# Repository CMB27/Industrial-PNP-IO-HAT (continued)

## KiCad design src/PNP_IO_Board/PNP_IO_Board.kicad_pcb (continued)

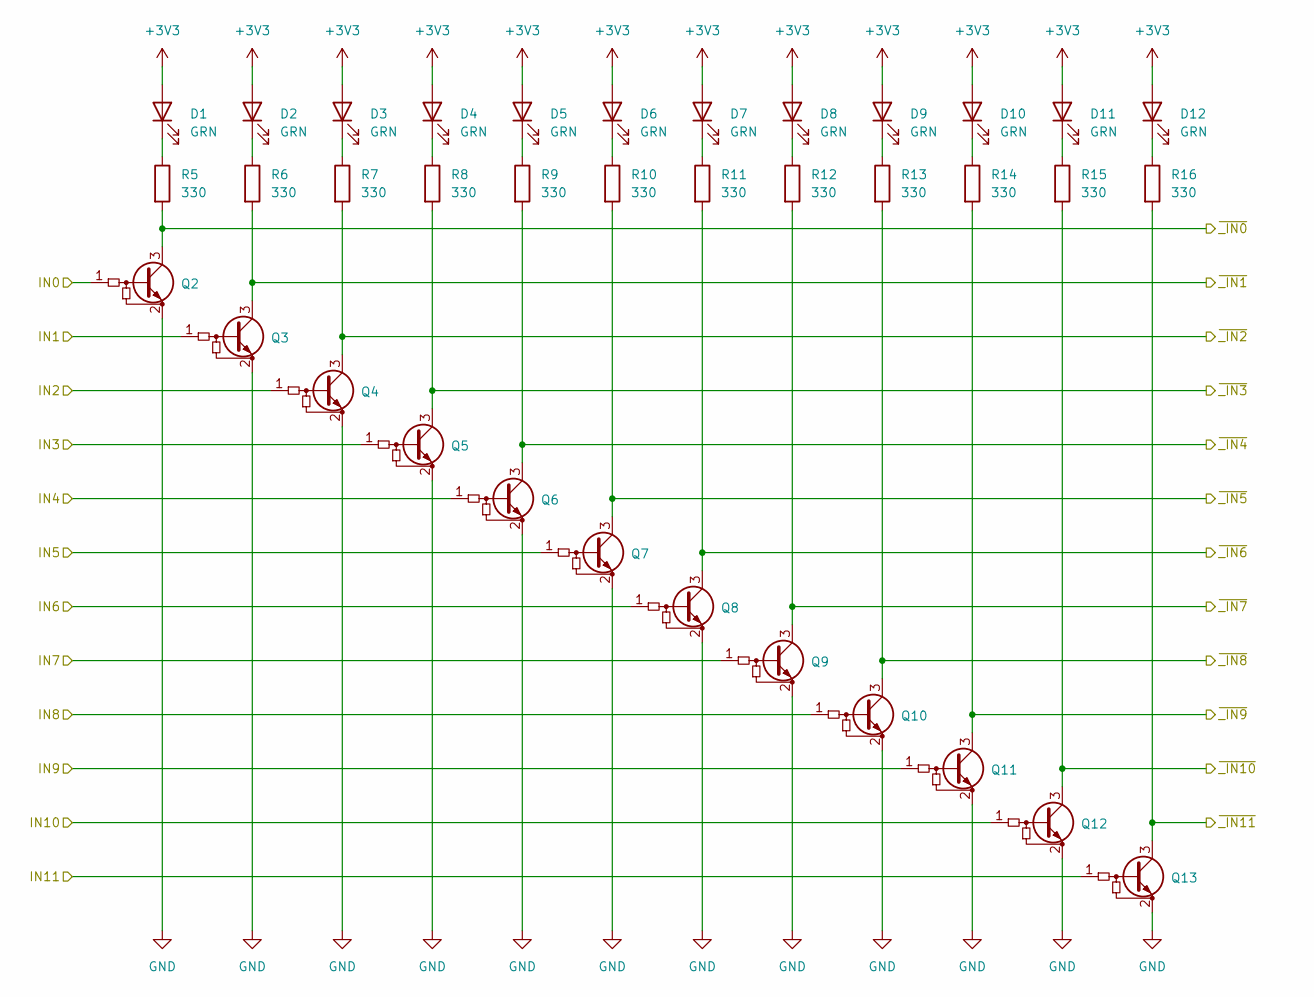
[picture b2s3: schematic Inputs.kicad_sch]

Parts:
D1, D2, D3, D4, D5, D6, D7, D8, D9, D10, D11, D12: GRN; LED_5mm_Green
Q2, Q3, Q4, Q5, Q6, Q7, Q8, Q9, Q10, Q11, Q12, Q13: Q_NPN_BRT_BEC; SOT-23
R5, R6, R7, R8, R9, R10, R11, R12, R13, R14, R15, R16: 330; R_1206_3216Metric_Pad1.30x1.75mm_HandSolder

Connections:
+3V3: D1.2 (A), D2.2 (A), D3.2 (A), D4.2 (A), D5.2 (A), D6.2 (A), D7.2 (A), D8.2 (A), D9.2 (A), D10.2 (A), D11.2 (A), D12.2 (A); also elsewhere on the board
/INPUTS/IN0: Q2.1 (B); also elsewhere on the board
/INPUTS/IN1: Q3.1 (B); also elsewhere on the board
/INPUTS/IN2: Q4.1 (B); also elsewhere on the board
/INPUTS/IN3: Q5.1 (B); also elsewhere on the board
/INPUTS/IN4: Q6.1 (B); also elsewhere on the board
/INPUTS/IN5: Q7.1 (B); also elsewhere on the board
/INPUTS/IN6: Q8.1 (B); also elsewhere on the board
/INPUTS/IN7: Q9.1 (B); also elsewhere on the board
/INPUTS/IN8: Q10.1 (B); also elsewhere on the board
/INPUTS/IN9: Q11.1 (B); also elsewhere on the board
/INPUTS/IN10: Q12.1 (B); also elsewhere on the board
/INPUTS/IN11: Q13.1 (B); also elsewhere on the board
/INPUTS/~_IN0: Q2.3 (C), R5.2; also elsewhere on the board
/INPUTS/~_IN1: Q3.3 (C), R6.2; also elsewhere on the board
/INPUTS/~_IN2: Q4.3 (C), R7.2; also elsewhere on the board
/INPUTS/~_IN3: Q5.3 (C), R8.2; also elsewhere on the board
/INPUTS/~_IN4: Q6.3 (C), R9.2; also elsewhere on the board
/INPUTS/~_IN5: Q7.3 (C), R10.2; also elsewhere on the board
/INPUTS/~_IN6: Q8.3 (C), R11.2; also elsewhere on the board
/INPUTS/~_IN7: Q9.3 (C), R12.2; also elsewhere on the board
/INPUTS/~_IN8: Q10.3 (C), R13.2; also elsewhere on the board
/INPUTS/~_IN9: Q11.3 (C), R14.2; also elsewhere on the board
/INPUTS/~_IN10: Q12.3 (C), R15.2; also elsewhere on the board
/INPUTS/~_IN11: Q13.3 (C), R16.2; also elsewhere on the board
GND: Q2.2 (E), Q3.2 (E), Q4.2 (E), Q5.2 (E), Q6.2 (E), Q7.2 (E), Q8.2 (E), Q9.2 (E), Q10.2 (E), Q11.2 (E), Q12.2 (E), Q13.2 (E); also elsewhere on the board
unnamed: D1.1 (K), R5.1
unnamed: D2.1 (K), R6.1
unnamed: D3.1 (K), R7.1
unnamed: D4.1 (K), R8.1
unnamed: D5.1 (K), R9.1
unnamed: D6.1 (K), R10.1
unnamed: D7.1 (K), R11.1
unnamed: D8.1 (K), R12.1
unnamed: D9.1 (K), R13.1
unnamed: D10.1 (K), R14.1
unnamed: D11.1 (K), R15.1
unnamed: D12.1 (K), R16.1

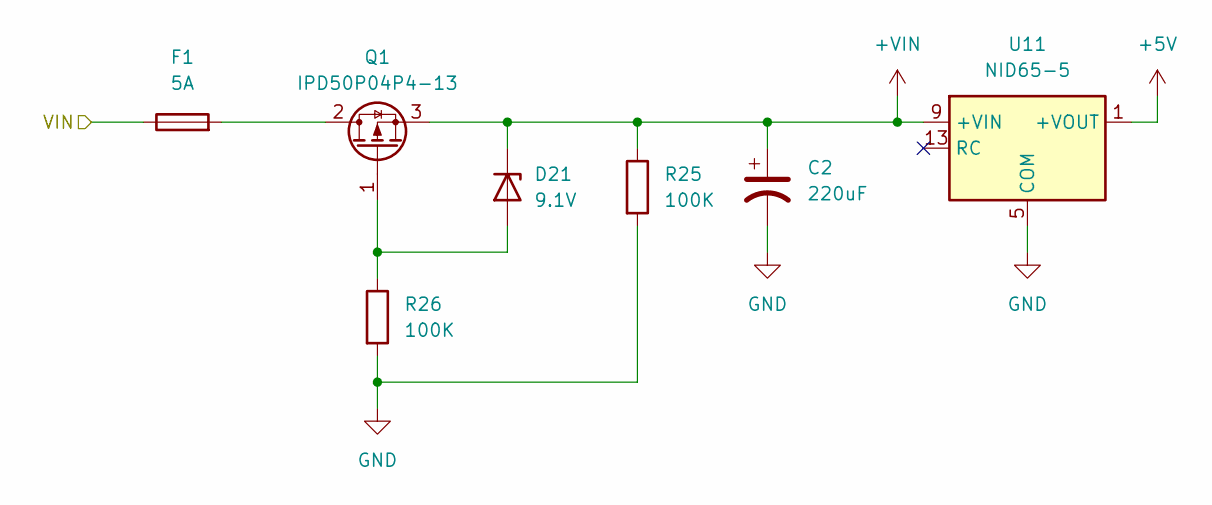
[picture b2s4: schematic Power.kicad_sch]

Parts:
C2: 220uF; CP_Radial_D10.0mm_P5.00mm; Part Number UVZ1H221MPD
D21: 9.1V; D_SOD-123; Part Number MMSZ5239BT1G
F1: 5A; Fuseholder_Littelfuse_Nano2_154x
Q1: IPD50P04P4-13; TO-252-2; Part Number IPD50P04P413ATMA2
R25, R26: 100K; R_1206_3216Metric_Pad1.30x1.75mm_HandSolder
U11: NID65-5; MEAN_WELL_NID100; Part Number NID65-5

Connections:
+5V: U11.1 (+VOUT), U11.2 (+VOUT), U11.3 (+VOUT), U11.4 (+VOUT); also elsewhere on the board
+VIN: C2.1, D21.1 (K), Q1.3 (S), R25.1, U11.9 (+VIN), U11.10 (+VIN); also elsewhere on the board
/POWER/VIN: F1.1; also elsewhere on the board
GND: C2.2, R25.2, R26.2, U11.5 (COM), U11.6 (COM), U11.7 (COM), U11.8 (COM); also elsewhere on the board
unnamed: D21.2 (A), Q1.1 (G), R26.1
unnamed: F1.2, Q1.2 (D)

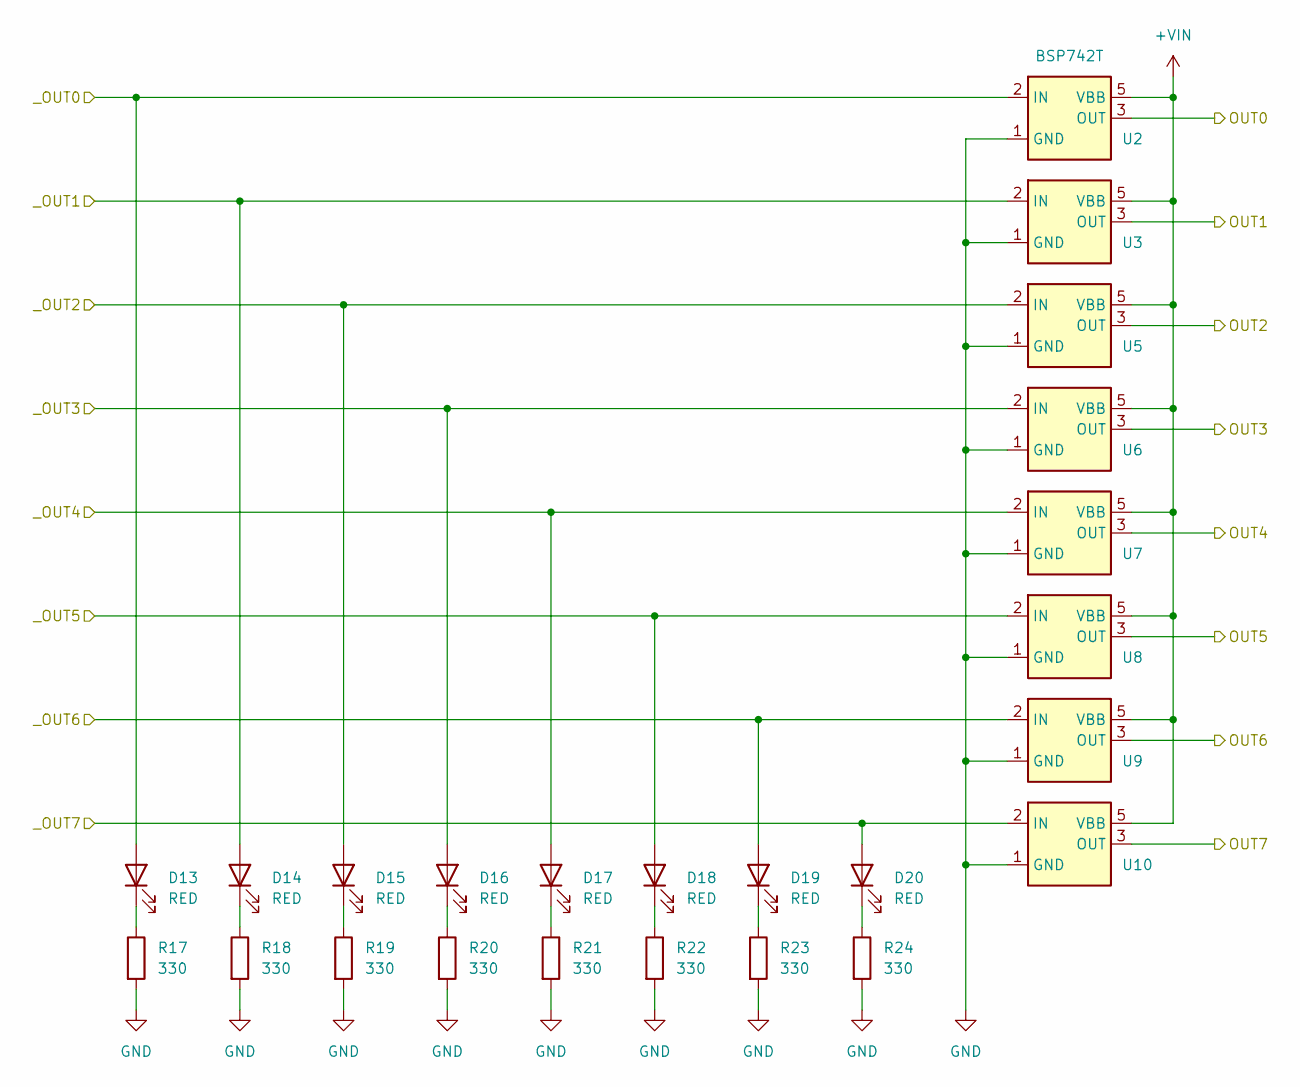
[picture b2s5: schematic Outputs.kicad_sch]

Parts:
D13, D14, D15, D16, D17, D18, D19, D20: RED; LED_5mm_Red; Part Number LTL2R3KRD-EM
R17, R18, R19, R20, R21, R22, R23, R24: 330; R_1206_3216Metric_Pad1.30x1.75mm_HandSolder
U2, U3, U5, U6, U7, U8, U9, U10: BSP742T; SOIC-8_3.9x4.9mm_P1.27mm; Part Number BSP742TXUMA1

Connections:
+VIN: U2.5 (VBB), U2.6 (VBB), U2.7 (VBB), U2.8 (VBB), U3.5 (VBB), U3.6 (VBB), U3.7 (VBB), U3.8 (VBB), U5.5 (VBB), U5.6 (VBB), U5.7 (VBB), U5.8 (VBB), U6.5 (VBB), U6.6 (VBB), U6.7 (VBB), U6.8 (VBB), U7.5 (VBB), U7.6 (VBB), U7.7 (VBB), U7.8 (VBB), U8.5 (VBB), U8.6 (VBB), U8.7 (VBB), U8.8 (VBB), U9.5 (VBB), U9.6 (VBB), U9.7 (VBB), U9.8 (VBB), U10.5 (VBB), U10.6 (VBB), U10.7 (VBB), U10.8 (VBB); also elsewhere on the board
/OUTPUTS/OUT0: U2.3 (OUT); also elsewhere on the board
/OUTPUTS/OUT1: U3.3 (OUT); also elsewhere on the board
/OUTPUTS/OUT2: U5.3 (OUT); also elsewhere on the board
/OUTPUTS/OUT3: U6.3 (OUT); also elsewhere on the board
/OUTPUTS/OUT4: U7.3 (OUT); also elsewhere on the board
/OUTPUTS/OUT5: U8.3 (OUT); also elsewhere on the board
/OUTPUTS/OUT6: U9.3 (OUT); also elsewhere on the board
/OUTPUTS/OUT7: U10.3 (OUT); also elsewhere on the board
/OUTPUTS/_OUT0: D13.2 (A), U2.2 (IN); also elsewhere on the board
/OUTPUTS/_OUT1: D14.2 (A), U3.2 (IN); also elsewhere on the board
/OUTPUTS/_OUT2: D15.2 (A), U5.2 (IN); also elsewhere on the board
/OUTPUTS/_OUT3: D16.2 (A), U6.2 (IN); also elsewhere on the board
/OUTPUTS/_OUT4: D17.2 (A), U7.2 (IN); also elsewhere on the board
/OUTPUTS/_OUT5: D18.2 (A), U8.2 (IN); also elsewhere on the board
/OUTPUTS/_OUT6: D19.2 (A), U9.2 (IN); also elsewhere on the board
/OUTPUTS/_OUT7: D20.2 (A), U10.2 (IN); also elsewhere on the board
GND: R17.2, R18.2, R19.2, R20.2, R21.2, R22.2, R23.2, R24.2, U2.1 (GND), U3.1 (GND), U5.1 (GND), U6.1 (GND), U7.1 (GND), U8.1 (GND), U9.1 (GND), U10.1 (GND); also elsewhere on the board
unnamed: D13.1 (K), R17.1
unnamed: D14.1 (K), R18.1
unnamed: D15.1 (K), R19.1
unnamed: D16.1 (K), R20.1
unnamed: D17.1 (K), R21.1
unnamed: D18.1 (K), R22.1
unnamed: D19.1 (K), R23.1
unnamed: D20.1 (K), R24.1

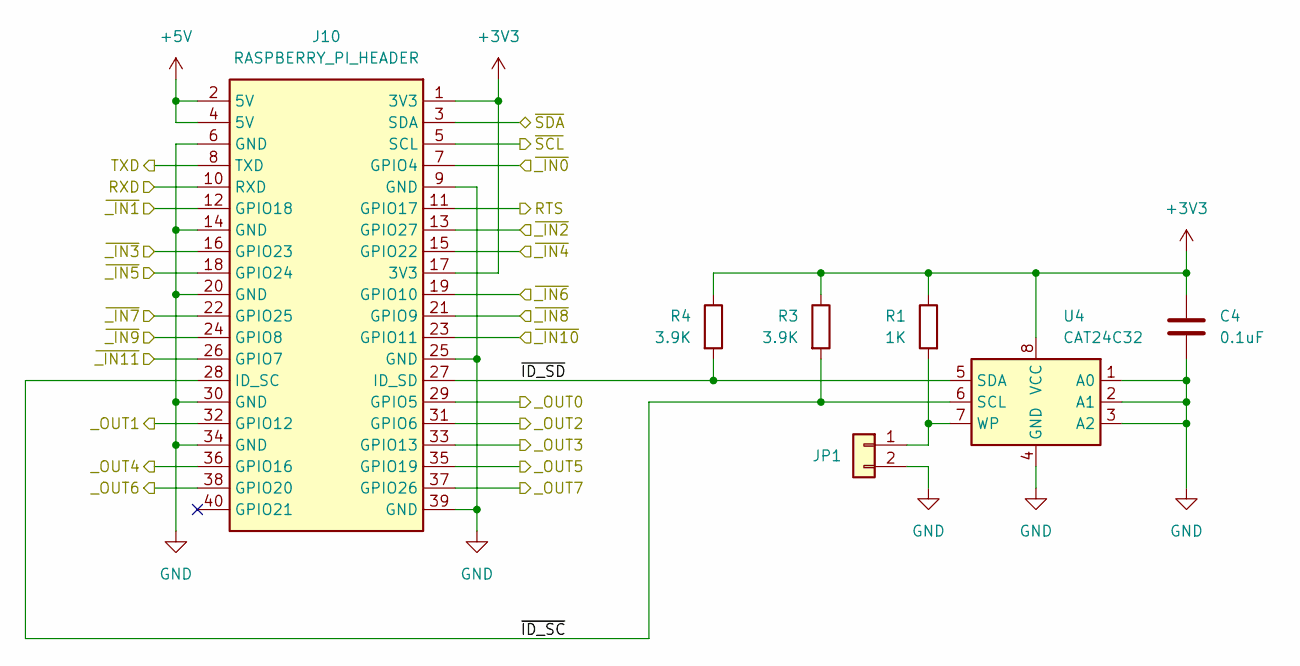
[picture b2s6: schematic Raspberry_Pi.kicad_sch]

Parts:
C4: 0.1uF; C_1206_3216Metric_Pad1.33x1.80mm_HandSolder
J10: RASPBERRY_PI_HEADER; Raspberry_Pi_Generic
JP1: Conn_01x02; PinHeader_1x02_P2.54mm_Vertical
R1: 1K; R_1206_3216Metric_Pad1.30x1.75mm_HandSolder
R3, R4: 3.9K; R_1206_3216Metric_Pad1.30x1.75mm_HandSolder
U4: CAT24C32; SOIC-8_3.9x4.9mm_P1.27mm

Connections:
+3V3: C4.1, J10.1 (3V3), J10.17 (3V3), R1.1, R3.1, R4.1, U4.8 (VCC); also elsewhere on the board
+5V: J10.2 (5V), J10.4 (5V); also elsewhere on the board
/INPUTS/~_IN0: J10.7 (GPIO4); also elsewhere on the board
/INPUTS/~_IN1: J10.12 (GPIO18); also elsewhere on the board
/INPUTS/~_IN2: J10.13 (GPIO27); also elsewhere on the board
/INPUTS/~_IN3: J10.16 (GPIO23); also elsewhere on the board
/INPUTS/~_IN4: J10.15 (GPIO22); also elsewhere on the board
/INPUTS/~_IN5: J10.18 (GPIO24); also elsewhere on the board
/INPUTS/~_IN6: J10.19 (GPIO10); also elsewhere on the board
/INPUTS/~_IN7: J10.22 (GPIO25); also elsewhere on the board
/INPUTS/~_IN8: J10.21 (GPIO9); also elsewhere on the board
/INPUTS/~_IN9: J10.24 (GPIO8); also elsewhere on the board
/INPUTS/~_IN10: J10.23 (GPIO11); also elsewhere on the board
/INPUTS/~_IN11: J10.26 (GPIO7); also elsewhere on the board
/OUTPUTS/_OUT0: J10.29 (GPIO5); also elsewhere on the board
/OUTPUTS/_OUT1: J10.32 (GPIO12); also elsewhere on the board
/OUTPUTS/_OUT2: J10.31 (GPIO6); also elsewhere on the board
/OUTPUTS/_OUT3: J10.33 (GPIO13); also elsewhere on the board
/OUTPUTS/_OUT4: J10.36 (GPIO16); also elsewhere on the board
/OUTPUTS/_OUT5: J10.35 (GPIO19); also elsewhere on the board
/OUTPUTS/_OUT6: J10.38 (GPIO20); also elsewhere on the board
/OUTPUTS/_OUT7: J10.37 (GPIO26); also elsewhere on the board
/RASPBERRY_PI/RTS: J10.11 (GPIO17); also elsewhere on the board
/RASPBERRY_PI/RXD: J10.10 (RXD); also elsewhere on the board
/RASPBERRY_PI/TXD: J10.8 (TXD); also elsewhere on the board
/RASPBERRY_PI/~ID_SC: J10.28 (ID_SC), R3.2, U4.6 (SCL)
/RASPBERRY_PI/~ID_SD: J10.27 (ID_SD), R4.2, U4.5 (SDA)
/RASPBERRY_PI/~SCL: J10.5 (SCL); also elsewhere on the board
/RASPBERRY_PI/~SDA: J10.3 (SDA); also elsewhere on the board
GND: C4.2, J10.6 (GND), J10.9 (GND), J10.14 (GND), J10.20 (GND), J10.25 (GND), J10.30 (GND), J10.34 (GND), J10.39 (GND), JP1.2, U4.1 (A0), U4.2 (A1), U4.3 (A2), U4.4 (GND); also elsewhere on the board
unnamed: JP1.1, R1.2, U4.7 (WP)

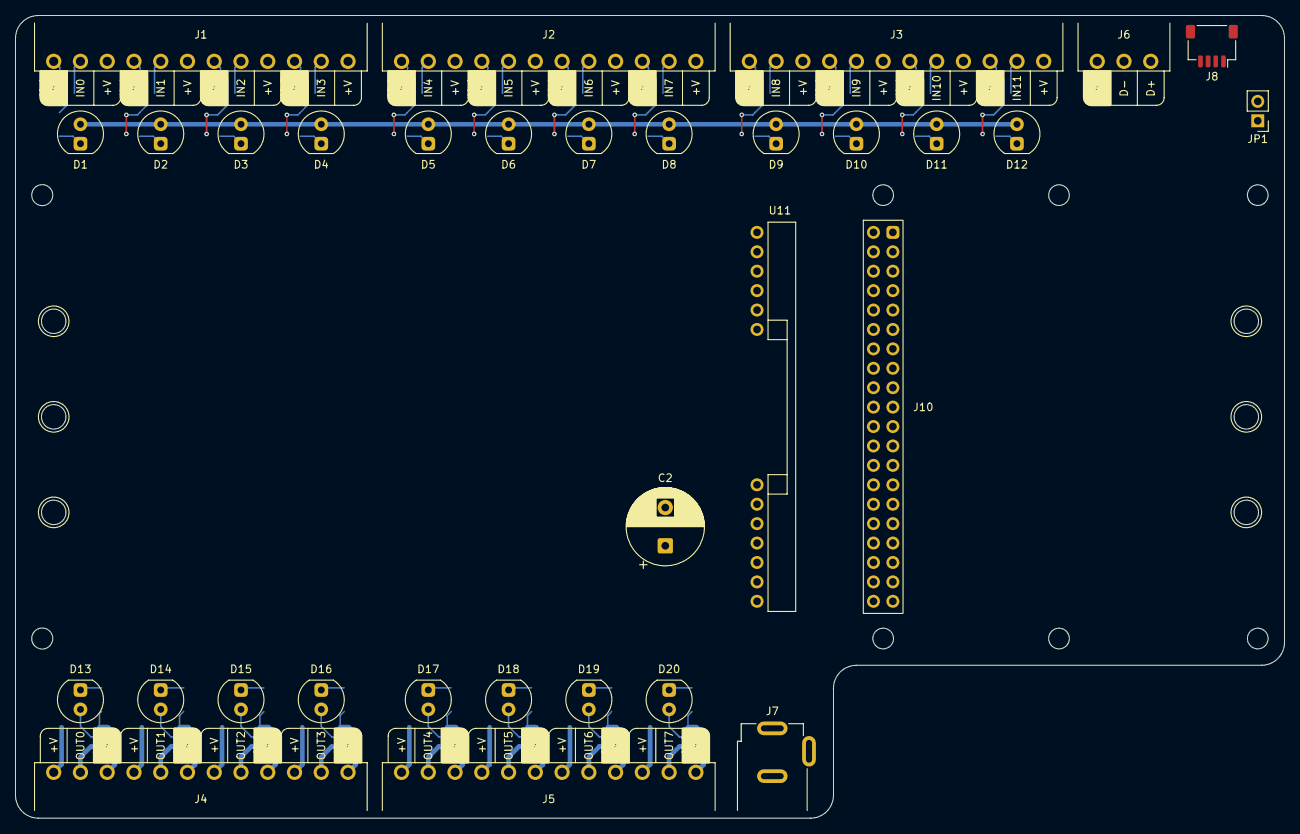
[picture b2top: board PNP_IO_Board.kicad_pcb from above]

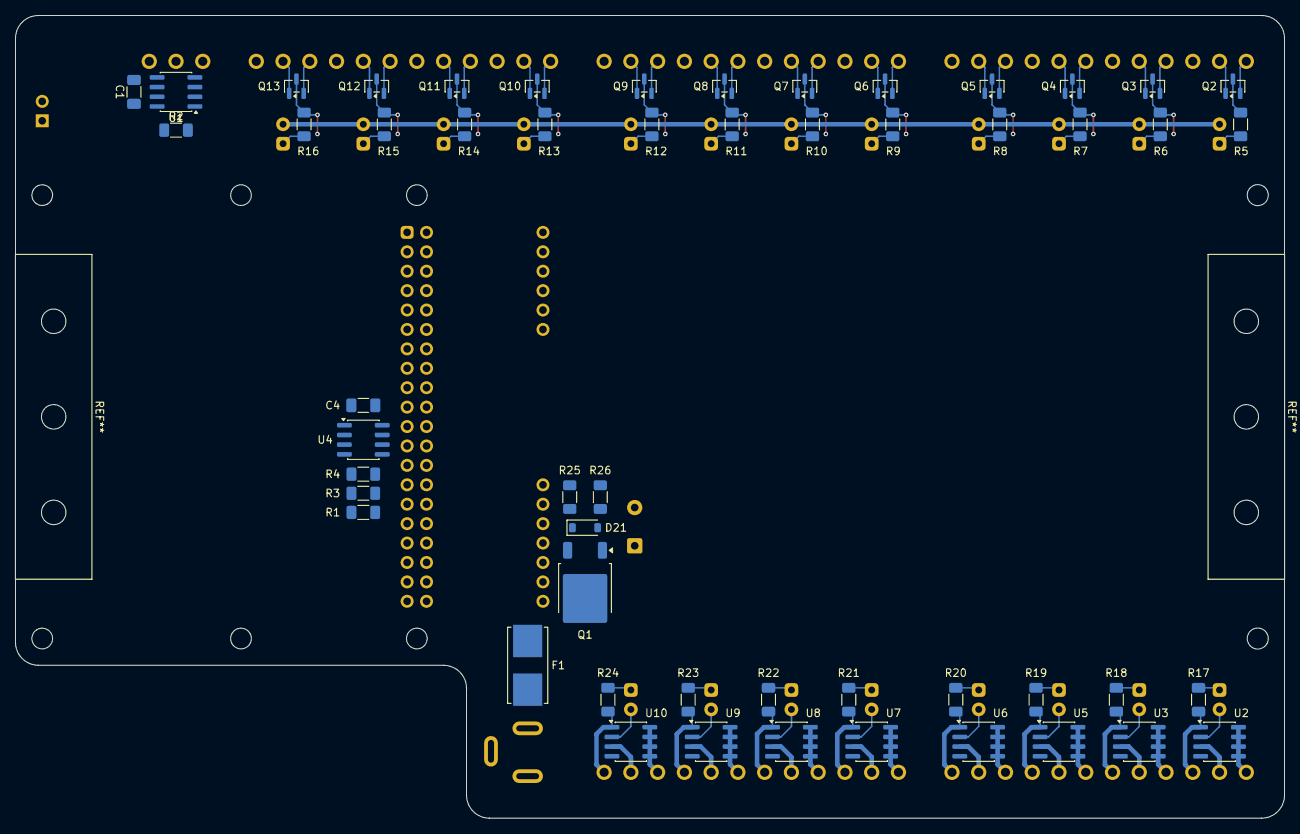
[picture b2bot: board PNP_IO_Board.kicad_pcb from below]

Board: 2 copper layers, 166.0 x 105.0 mm, 85 parts (53 on the bottom side), 77 nets.
